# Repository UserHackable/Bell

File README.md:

## Bell 

### Board dimensions

* (250000, 200000) original units
* (2.5000, 2.0000) inches
* (63.5000, 50.8000) mm

| Front | Back |
| --- | --- |
|  |  |

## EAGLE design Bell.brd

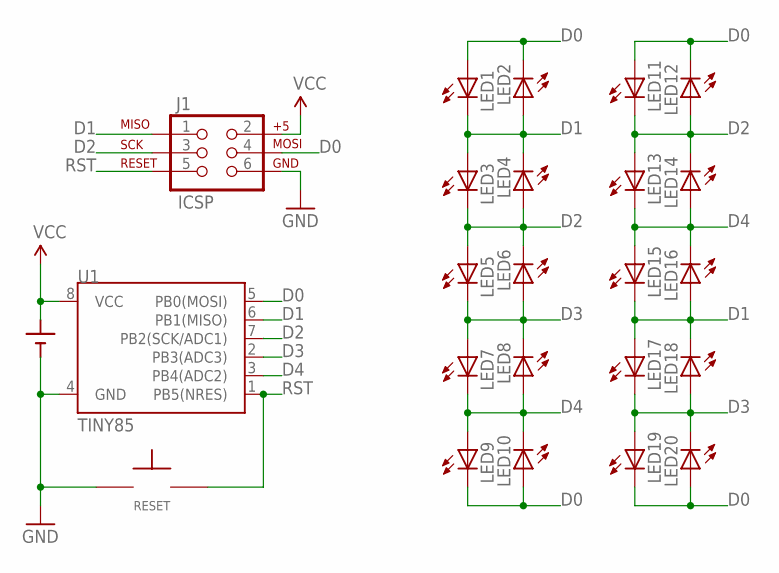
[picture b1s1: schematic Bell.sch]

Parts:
BATT: CR2032; CR2032-THRU
J1: ICSP; 2X3-NS
LED1, LED2, LED3, LED4, LED5, LED6, LED7, LED8, LED9, LED10, LED11, LED12, LED13, LED14, LED15, LED16, LED17, LED18, LED19, LED20: LED5MM
RESET: TAC_SPST_NO
U1: TINY85; DIP08

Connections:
D0: J1.4 (MOSI), LED1.A, LED2.K (C), LED9.K (C), LED10.A, LED11.A, LED12.K (C), LED19.K (C), LED20.A, U1.5 (PB0(MOSI))
D1: J1.1 (MISO), LED1.K (C), LED2.A, LED3.A, LED4.K (C), LED15.K (C), LED16.A, LED17.A, LED18.K (C), U1.6 (PB1(MISO))
D2: J1.3 (SCK), LED3.K (C), LED4.A, LED5.A, LED6.K (C), LED11.K (C), LED12.A, LED13.A, LED14.K (C), U1.7 (PB2(SCK/ADC1))
D3: LED5.K (C), LED6.A, LED7.A, LED8.K (C), LED17.K (C), LED18.A, LED19.A, LED20.K (C), U1.2 (PB3(ADC3))
D4: LED7.K (C), LED8.A, LED9.A, LED10.K (C), LED13.K (C), LED14.A, LED15.A, LED16.K (C), U1.3 (PB4(ADC2))
GND: BATT.-, J1.6 (GND), RESET.P$1, U1.4 (GND)
RST: J1.5 (RST), RESET.P$2, U1.1 (PB5(NRES))
VCC: BATT.+1 (+), J1.2 (V+), U1.8 (VCC)

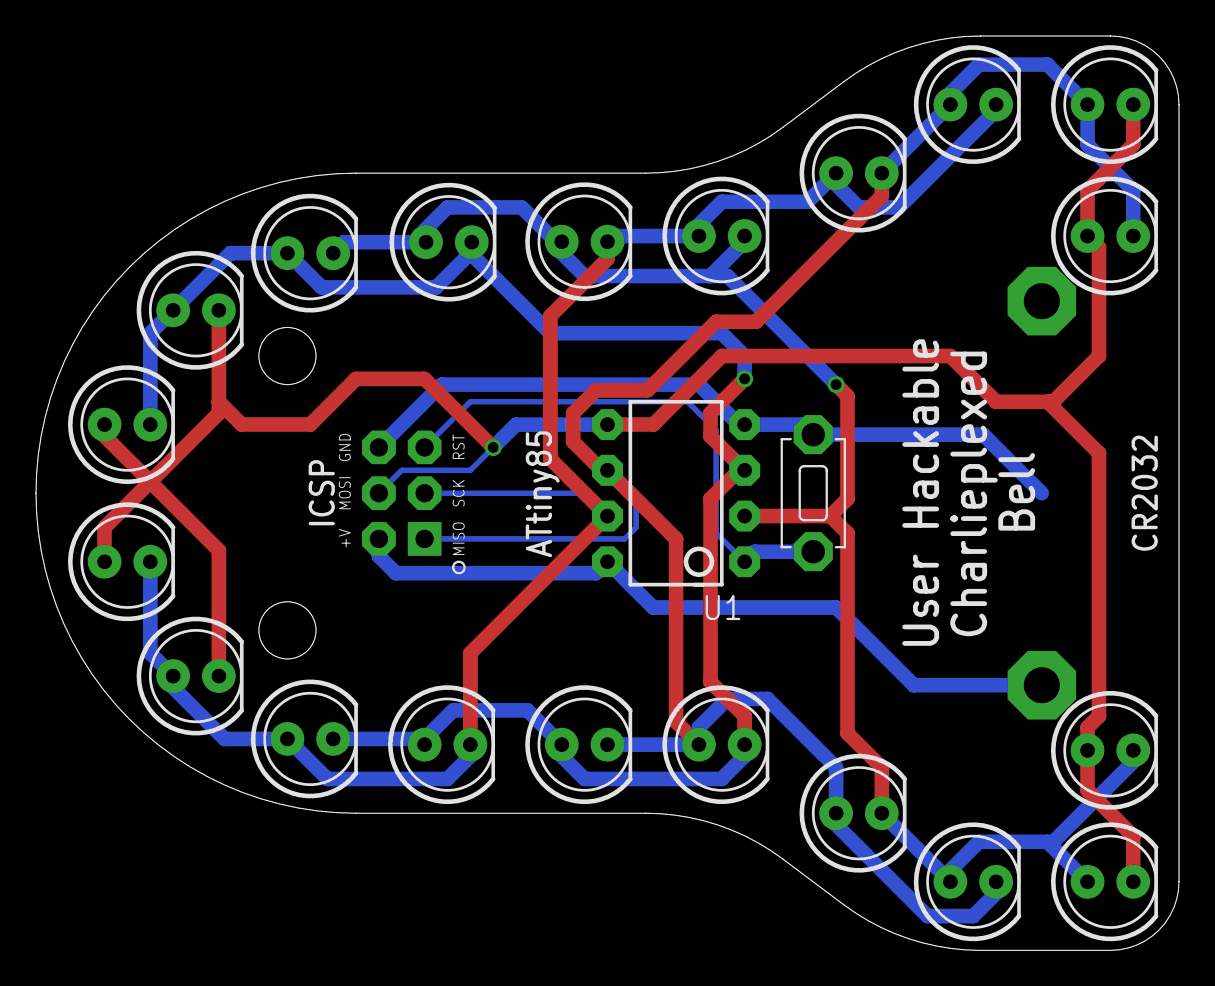
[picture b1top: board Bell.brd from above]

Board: 2 copper layers, 63.5 x 50.8 mm, 24 parts (1 on the bottom side), 8 nets.

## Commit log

2016-04-06 rotating images
2016-04-07 from Makefile

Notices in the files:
parts and their libraries:
SparkFun-DigitalIC: Licensing: Creative Commons ShareAlike 4.0 International - https://creativecommons.org/licenses/by-sa/4.0
